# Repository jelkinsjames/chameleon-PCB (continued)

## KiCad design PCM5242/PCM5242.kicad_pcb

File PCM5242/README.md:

# PCM 5242

The [PCM5242](https://www.ti.com/product/PCM5242) is a 32-bit stereo DAC IC chip. Its datasheet can be found and downloaded [here](chameleon-PCB/PCM5242/pcm5242.pdf).

Here is a block diagram of the 5242 (taken from the datasheet):

The chip is capable of several sophisticated DSP processess organic to itself, but that is not what we are going to use it for in this project. 
More details about why and how we are using this chip are to follow. We will start with the basic outline of the chip to a level of understanding that you will need to operate it, and then move into details about how exactly it is used in this application. At the end of this document, you will be able to use the 5242 with the Chameleon to achieve your audio-processing goals.

# Inputs

# Outputs

# Clocking

# PCB Design Details

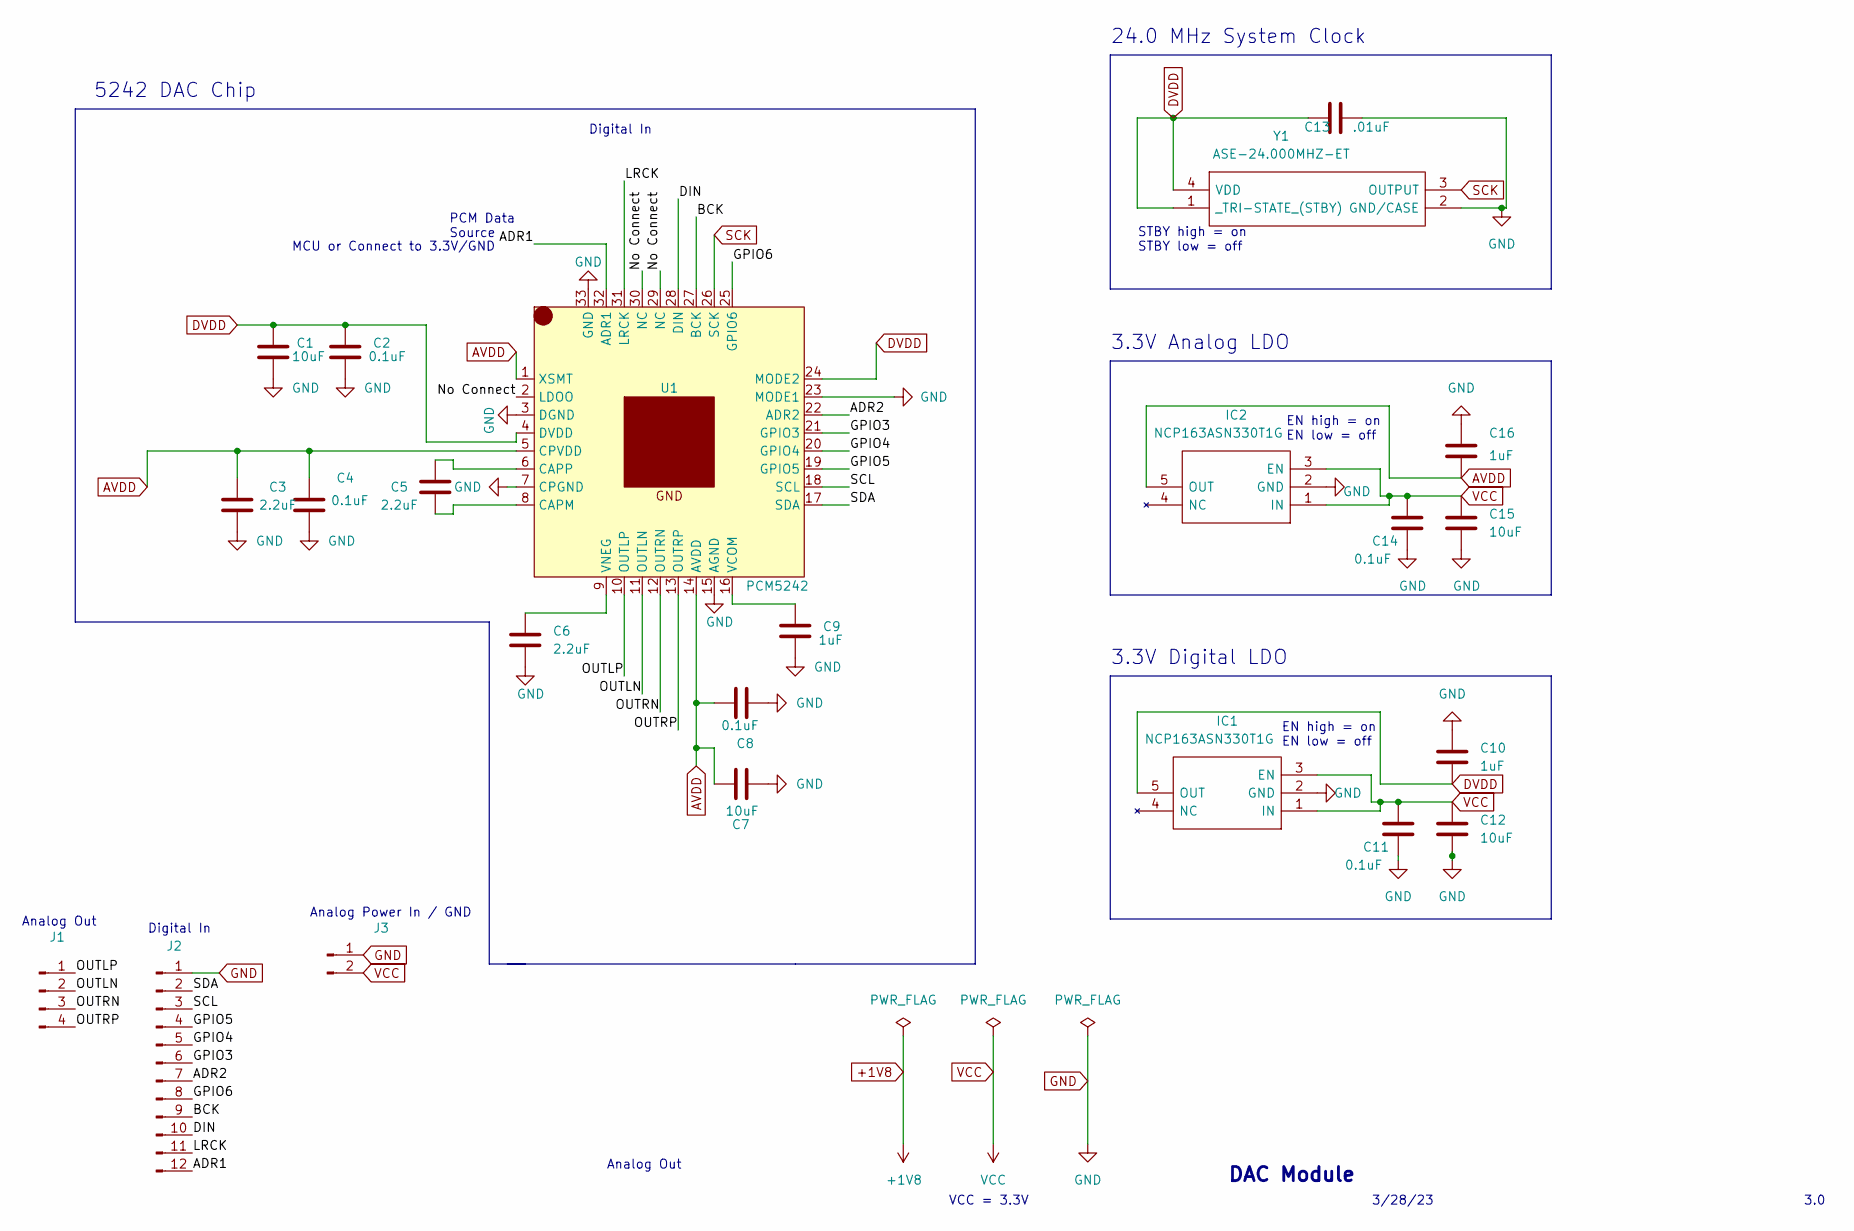
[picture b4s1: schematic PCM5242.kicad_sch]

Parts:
C1, C7, C12, C15: 10uF; C_0603_1608Metric_Pad1.08x0.95mm_HandSolder
C2, C4, C8, C11, C14: 0.1uF; C_0603_1608Metric_Pad1.08x0.95mm_HandSolder
C3, C5, C6: 2.2uF; C_0603_1608Metric_Pad1.08x0.95mm_HandSolder
C9, C10, C16: 1uF; C_0603_1608Metric_Pad1.08x0.95mm_HandSolder
C13: .01uF; C_0603_1608Metric_Pad1.08x0.95mm_HandSolder
IC1, IC2: NCP163ASN330T1G; SOT95P280X145-5N; Manufacturer_Part_Number NCP163ASN330T1G; Mouser Part Number 863-NCP163ASN330T1G
J1: Conn_01x04_Male; PinHeader_1x04_P2.54mm_Vertical
J2: Conn_01x12_Male; PinHeader_1x12_P2.54mm_Vertical
J3: d; PinHeader_1x02_P2.54mm_Vertical
U1: PCM5242; HVQFN-32-1EP_5x5mm_P0.5mm_EP3.1x3.1mm
Y1: ASE-24.000MHZ-ET; ASE24000MHZET; Manufacturer_Part_Number ASE-24.000MHZ-ET; Mouser Part Number 815-ASE24.000MHZET

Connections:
/ADR1: J2.12, U1.32 (ADR1)
/ADR2: J2.7, U1.22 (ADR2)
/BCK: J2.9, U1.27 (BCK)
/DIN: J2.10, U1.28 (DIN)
/GPIO3: J2.6, U1.21 (GPIO3)
/GPIO4: J2.5, U1.20 (GPIO4)
/GPIO5: J2.4, U1.19 (GPIO5)
/GPIO6: J2.8, U1.25 (GPIO6)
/LRCK: J2.11, U1.31 (LRCK)
/No Connect: U1.2 (LDOO), U1.29 (NC), U1.30 (NC)
/OUTLN: J1.2, U1.11 (OUTLN)
/OUTLP: J1.1, U1.10 (OUTLP)
/OUTRN: J1.3, U1.12 (OUTRN)
/OUTRP: J1.4, U1.13 (OUTRP)
/SCL: J2.3, U1.18 (SCL)
/SDA: J2.2, U1.17 (SDA)
AVDD: C3.1, C4.1, C7.1, C8.1, C16.2, IC2.5 (OUT), U1.1 (XSMT), U1.5 (CPVDD), U1.14 (AVDD)
DVDD: C1.2, C2.1, C10.2, C13.1, IC1.5 (OUT), U1.4 (DVDD), U1.24 (MODE2), Y1.1 (_TRI-STATE_(STBY)), Y1.4 (VDD)
GND: C1.1, C2.2, C3.2, C4.2, C6.2, C7.2, C8.2, C9.2, C10.1, C11.2, C12.2, C13.2, C14.2, C15.2, C16.1, IC1.2 (GND), IC2.2 (GND), J2.1, J3.1, U1.3 (DGND), U1.7 (CPGND), U1.15 (AGND), U1.23 (MODE1), U1.33 (GND), Y1.2 (GND/CASE)
unnamed: C5.1, U1.6 (CAPP)
unnamed: C5.2, U1.8 (CAPM)
unnamed: C6.1, U1.9 (VNEG)
unnamed: C9.1, U1.16 (VCOM)
SCK: U1.26 (SCK), Y1.3 (OUTPUT)
VCC: C11.1, C12.1, C14.1, C15.1, IC1.1 (IN), IC1.3 (EN), IC2.1 (IN), IC2.3 (EN), J3.2

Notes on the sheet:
Analog Out
Digital In
EN high = on EN low = off
3.0
Analog Power In / GND
3.3V Analog LDO
MCU or Connect to 3.3V/GND
24.0 MHz System Clock
STBY high = on STBY low = off
PCM Data Source
DAC Module
VCC = 3.3V
3.3V Digital LDO
Analog Out
Digital In
5242 DAC Chip
3/28/23

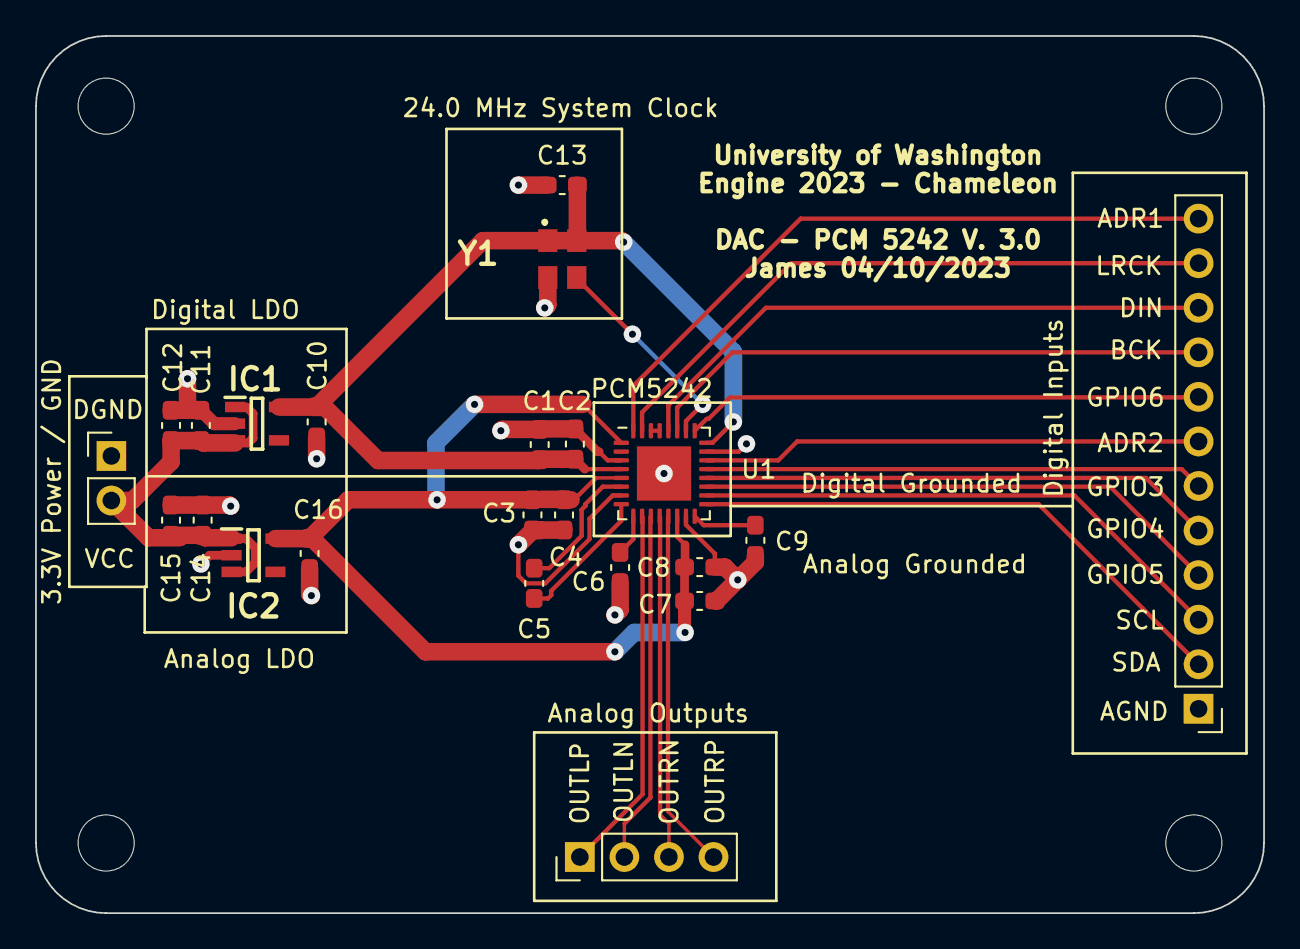
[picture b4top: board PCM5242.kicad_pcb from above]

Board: 2 copper layers, 70.0 x 50.0 mm, 23 parts (0 on the bottom side), 25 nets.

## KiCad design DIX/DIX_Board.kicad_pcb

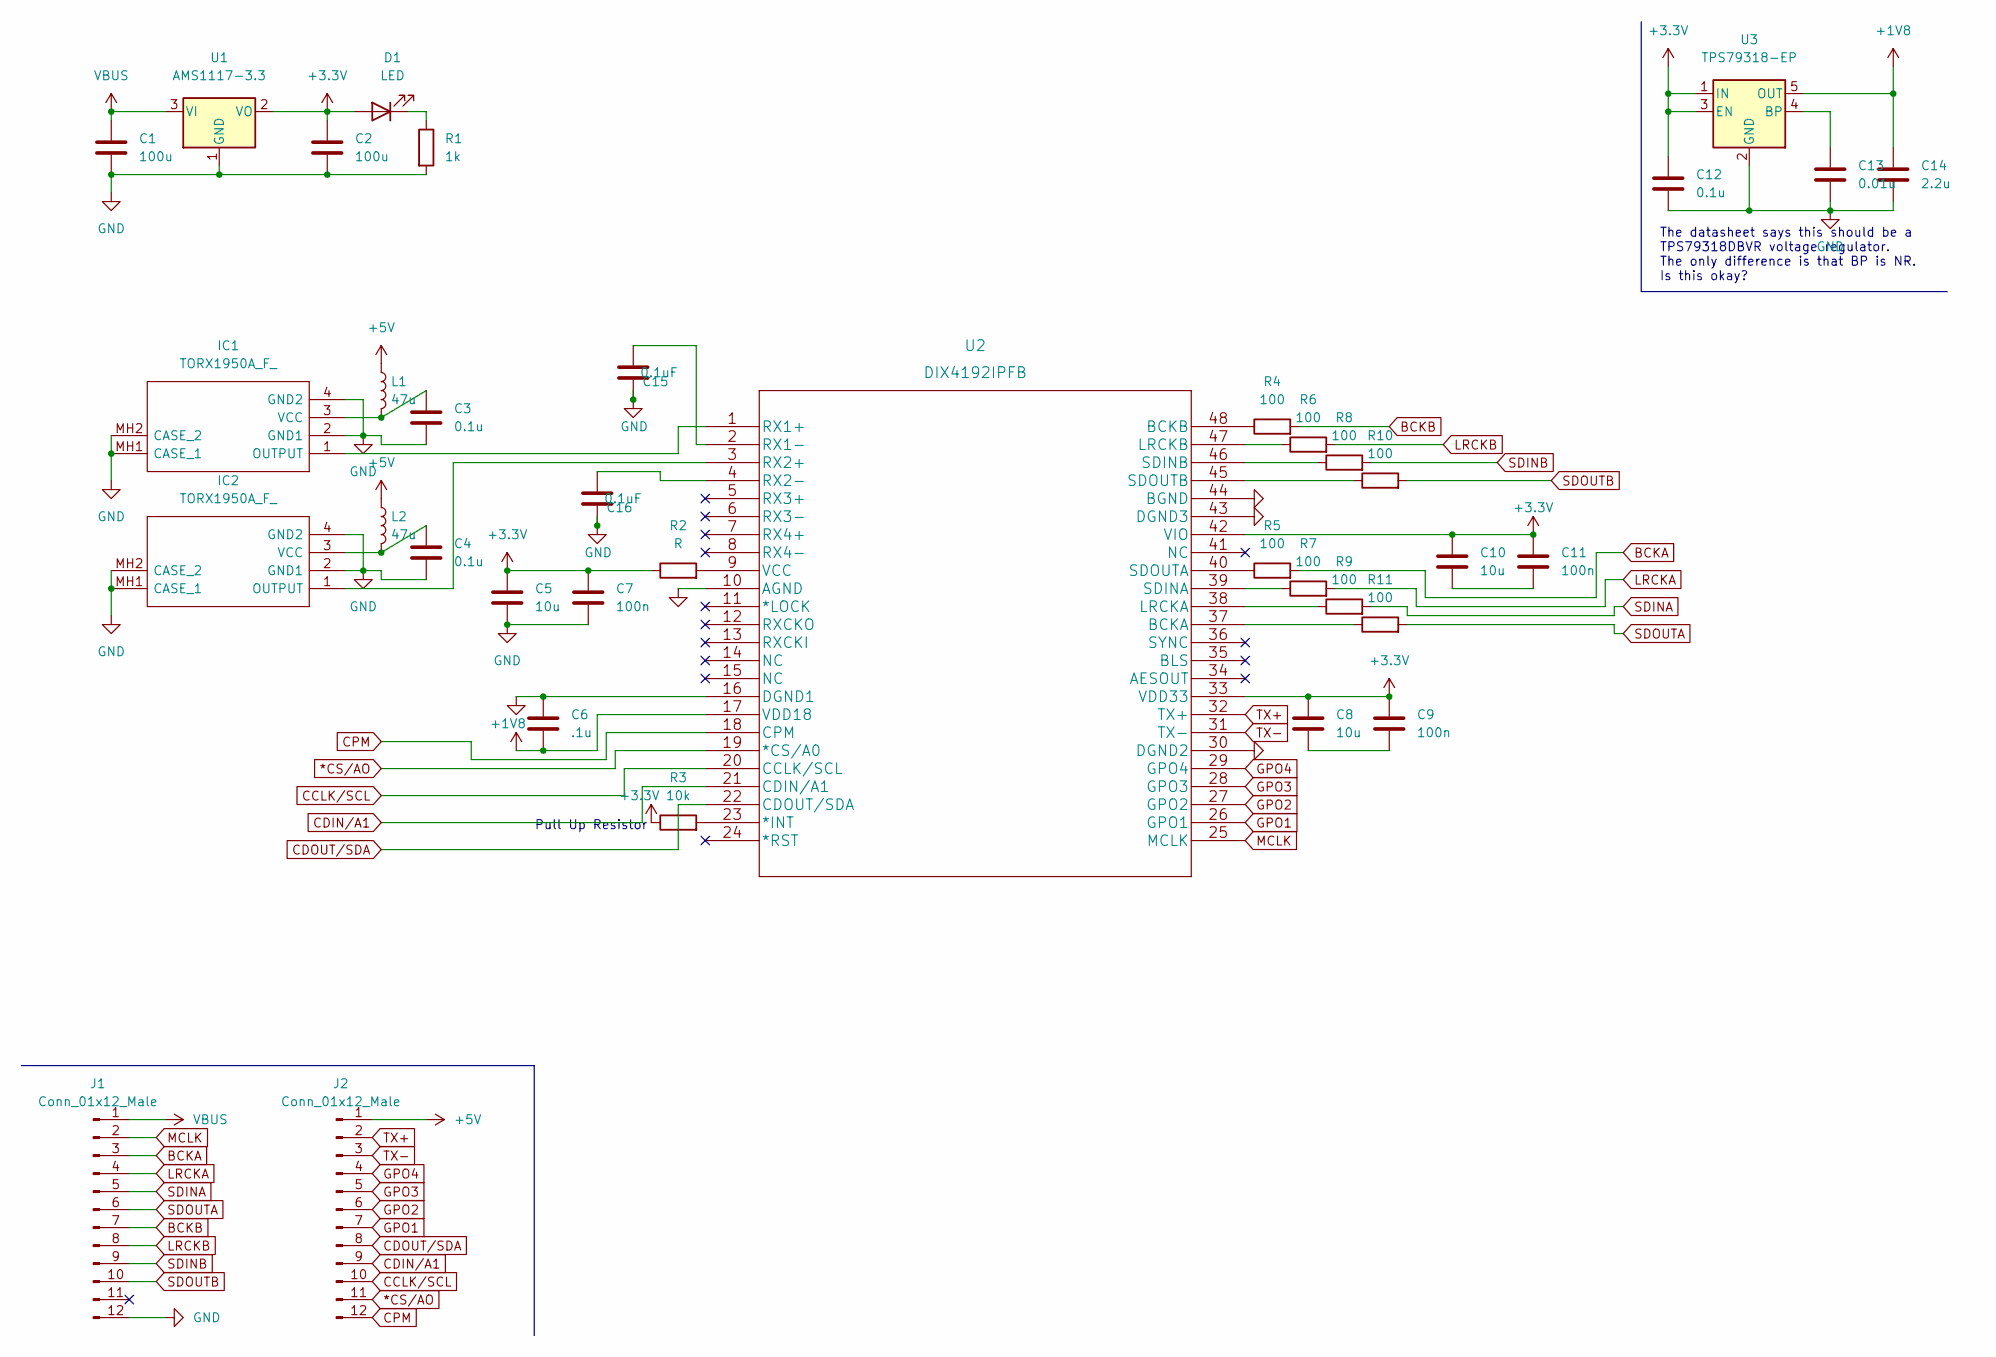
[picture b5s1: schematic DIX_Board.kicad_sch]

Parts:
C1, C2: 100u; C_0805_2012Metric_Pad1.18x1.45mm_HandSolder
C3, C4: 0.1u; C_0805_2012Metric_Pad1.18x1.45mm_HandSolder
C5, C8, C10: 10u; C_0805_2012Metric
C6: .1u; C_0805_2012Metric
C7, C9, C11: 100n; C_0805_2012Metric
C12: 0.1u; C_0805_2012Metric
C13: 0.01u; C_0805_2012Metric
C14: 2.2u; C_0805_2012Metric
C15, C16: 0.1uF; C_0603_1608Metric_Pad1.08x0.95mm_HandSolder
D1: LED; LED_D8.0mm
IC1, IC2: TORX1950A_F_; Reverb_BTDR-1H; Mouser Part Number 71-TORX1950A(F)
J1, J2: Conn_01x12_Male; PinHeader_1x12_P1.27mm_Vertical
L1, L2: 47u; L_0805_2012Metric_Pad1.05x1.20mm_HandSolder
R1: 1k; R_0805_2012Metric_Pad1.20x1.40mm_HandSolder
R2: R; R_0805_2012Metric_Pad1.20x1.40mm_HandSolder
R3: 10k; R_0805_2012Metric_Pad1.20x1.40mm_HandSolder
R4, R5, R6, R7, R8, R9, R10, R11: 100; R_0805_2012Metric_Pad1.20x1.40mm_HandSolder
U1: AMS1117-3.3; SOT-223-3_TabPin2
U2: DIX4192IPFB
U3: TPS79318-EP; SOT-23-5

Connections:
*CS/AO: J2.11, U2.19 (*CS/A0)
+1V8: C6.2, C14.1, U2.17 (VDD18), U3.5 (OUT)
+3.3V: C2.1, C5.1, C7.1, C8.1, C9.1, C10.1, C11.1, C12.1, D1.2 (A), R2.1, R3.1, U1.2 (VO), U2.33 (VDD33), U2.42 (VIO), U3.1 (IN), U3.3 (EN)
+5V: J2.1, L1.1, L2.1
BCKA: J1.3, R5.2
BCKB: J1.7, R4.2
CCLK/SCL: J2.10, U2.20 (CCLK/SCL)
CDIN/A1: J2.9, U2.21 (CDIN/A1)
CDOUT/SDA: J2.8, U2.22 (CDOUT/SDA)
CPM: J2.12, U2.18 (CPM)
GND: C1.2, C2.2, C3.2, C4.2, C5.2, C6.1, C7.2, C12.2, C13.2, C14.2, C15.1, C16.1, IC1.2 (GND1), IC1.4 (GND2), IC1.MH1 (CASE_1), IC1.MH2 (CASE_2), IC2.2 (GND1), IC2.4 (GND2), IC2.MH1 (CASE_1), IC2.MH2 (CASE_2), J1.12, R1.2, U1.1 (GND), U2.10 (AGND), U2.16 (DGND1), U2.30 (DGND2), U2.43 (DGND3), U2.44 (BGND), U3.2 (GND)
GPO1: J2.7, U2.26 (GPO1)
GPO2: J2.6, U2.27 (GPO2)
GPO3: J2.5, U2.28 (GPO3)
GPO4: J2.4, U2.29 (GPO4)
LRCKA: J1.4, R7.2
LRCKB: J1.8, R6.2
MCLK: J1.2, U2.25 (MCLK)
unnamed: C3.1, IC1.3 (VCC), L1.2
unnamed: C4.1, IC2.3 (VCC), L2.2
unnamed: C8.2, C9.2
unnamed: C10.2, C11.2
unnamed: C13.1, U3.4 (BP)
unnamed: C15.2, U2.2 (RX1-)
unnamed: C16.2, U2.4 (RX2-)
unnamed: D1.1 (K), R1.1
unnamed: IC1.1 (OUTPUT), U2.1 (RX1+)
unnamed: IC2.1 (OUTPUT), U2.3 (RX2+)
unnamed: R2.2, U2.9 (VCC)
unnamed: R3.2, U2.23 (*INT)
unnamed: R4.1, U2.48 (BCKB)
unnamed: R5.1, U2.40 (SDOUTA)
unnamed: R6.1, U2.47 (LRCKB)
unnamed: R7.1, U2.39 (SDINA)
unnamed: R8.1, U2.46 (SDINB)
unnamed: R9.1, U2.38 (LRCKA)
unnamed: R10.1, U2.45 (SDOUTB)
unnamed: R11.1, U2.37 (BCKA)
SDINA: J1.5, R9.2
SDINB: J1.9, R8.2
SDOUTA: J1.6, R11.2
SDOUTB: J1.10, R10.2
TX+: J2.2, U2.32 (TX+)
TX-: J2.3, U2.31 (TX-)
VBUS: C1.1, J1.1, U1.3 (VI)

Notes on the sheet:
The datasheet says this should be a TPS79318DBVR voltage regulator. The only difference is that BP is NR. Is this okay?
Pull Up Resistor

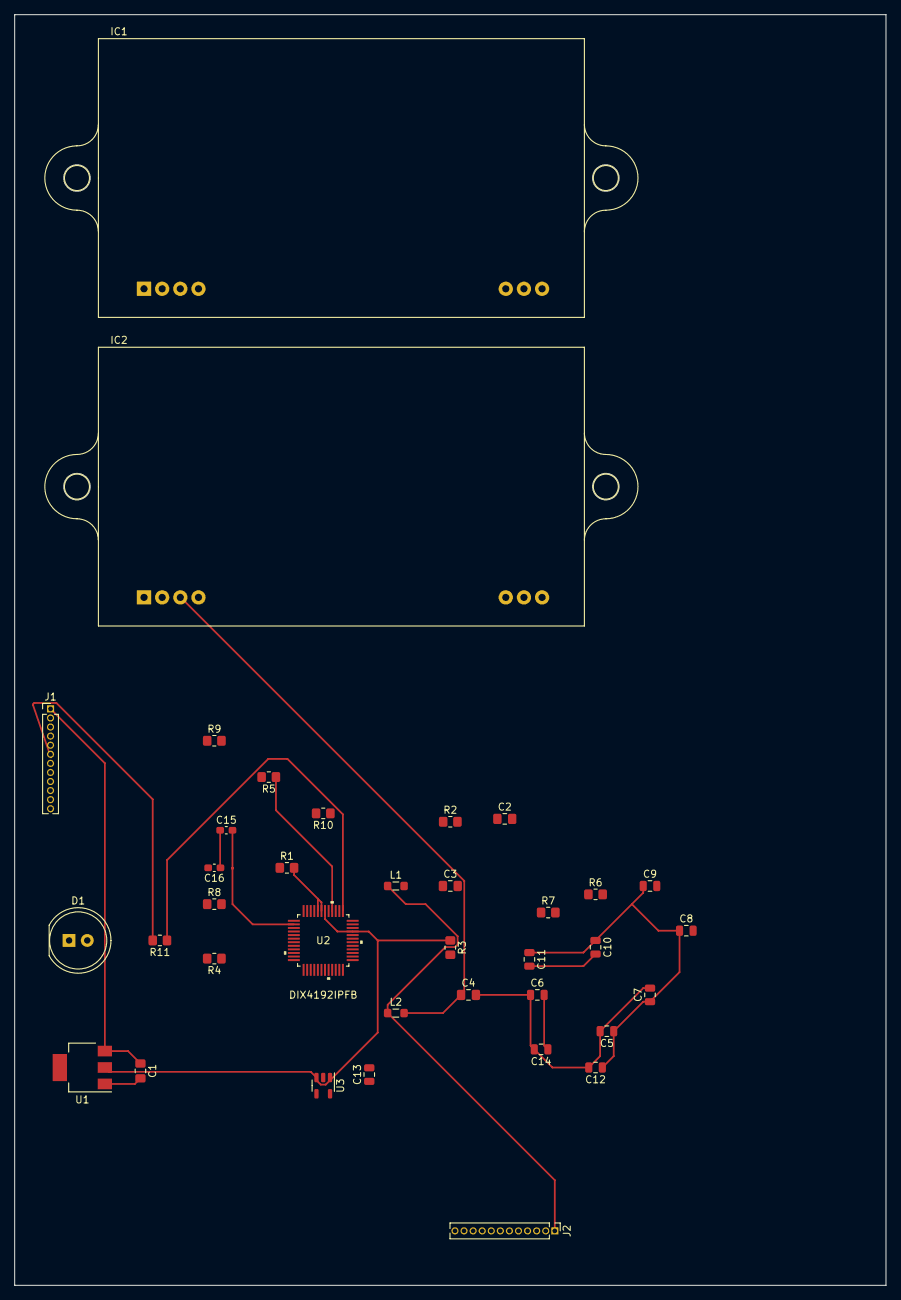
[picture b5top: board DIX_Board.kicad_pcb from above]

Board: 2 copper layers, 121.9 x 177.8 mm, 37 parts (0 on the bottom side), 45 nets.

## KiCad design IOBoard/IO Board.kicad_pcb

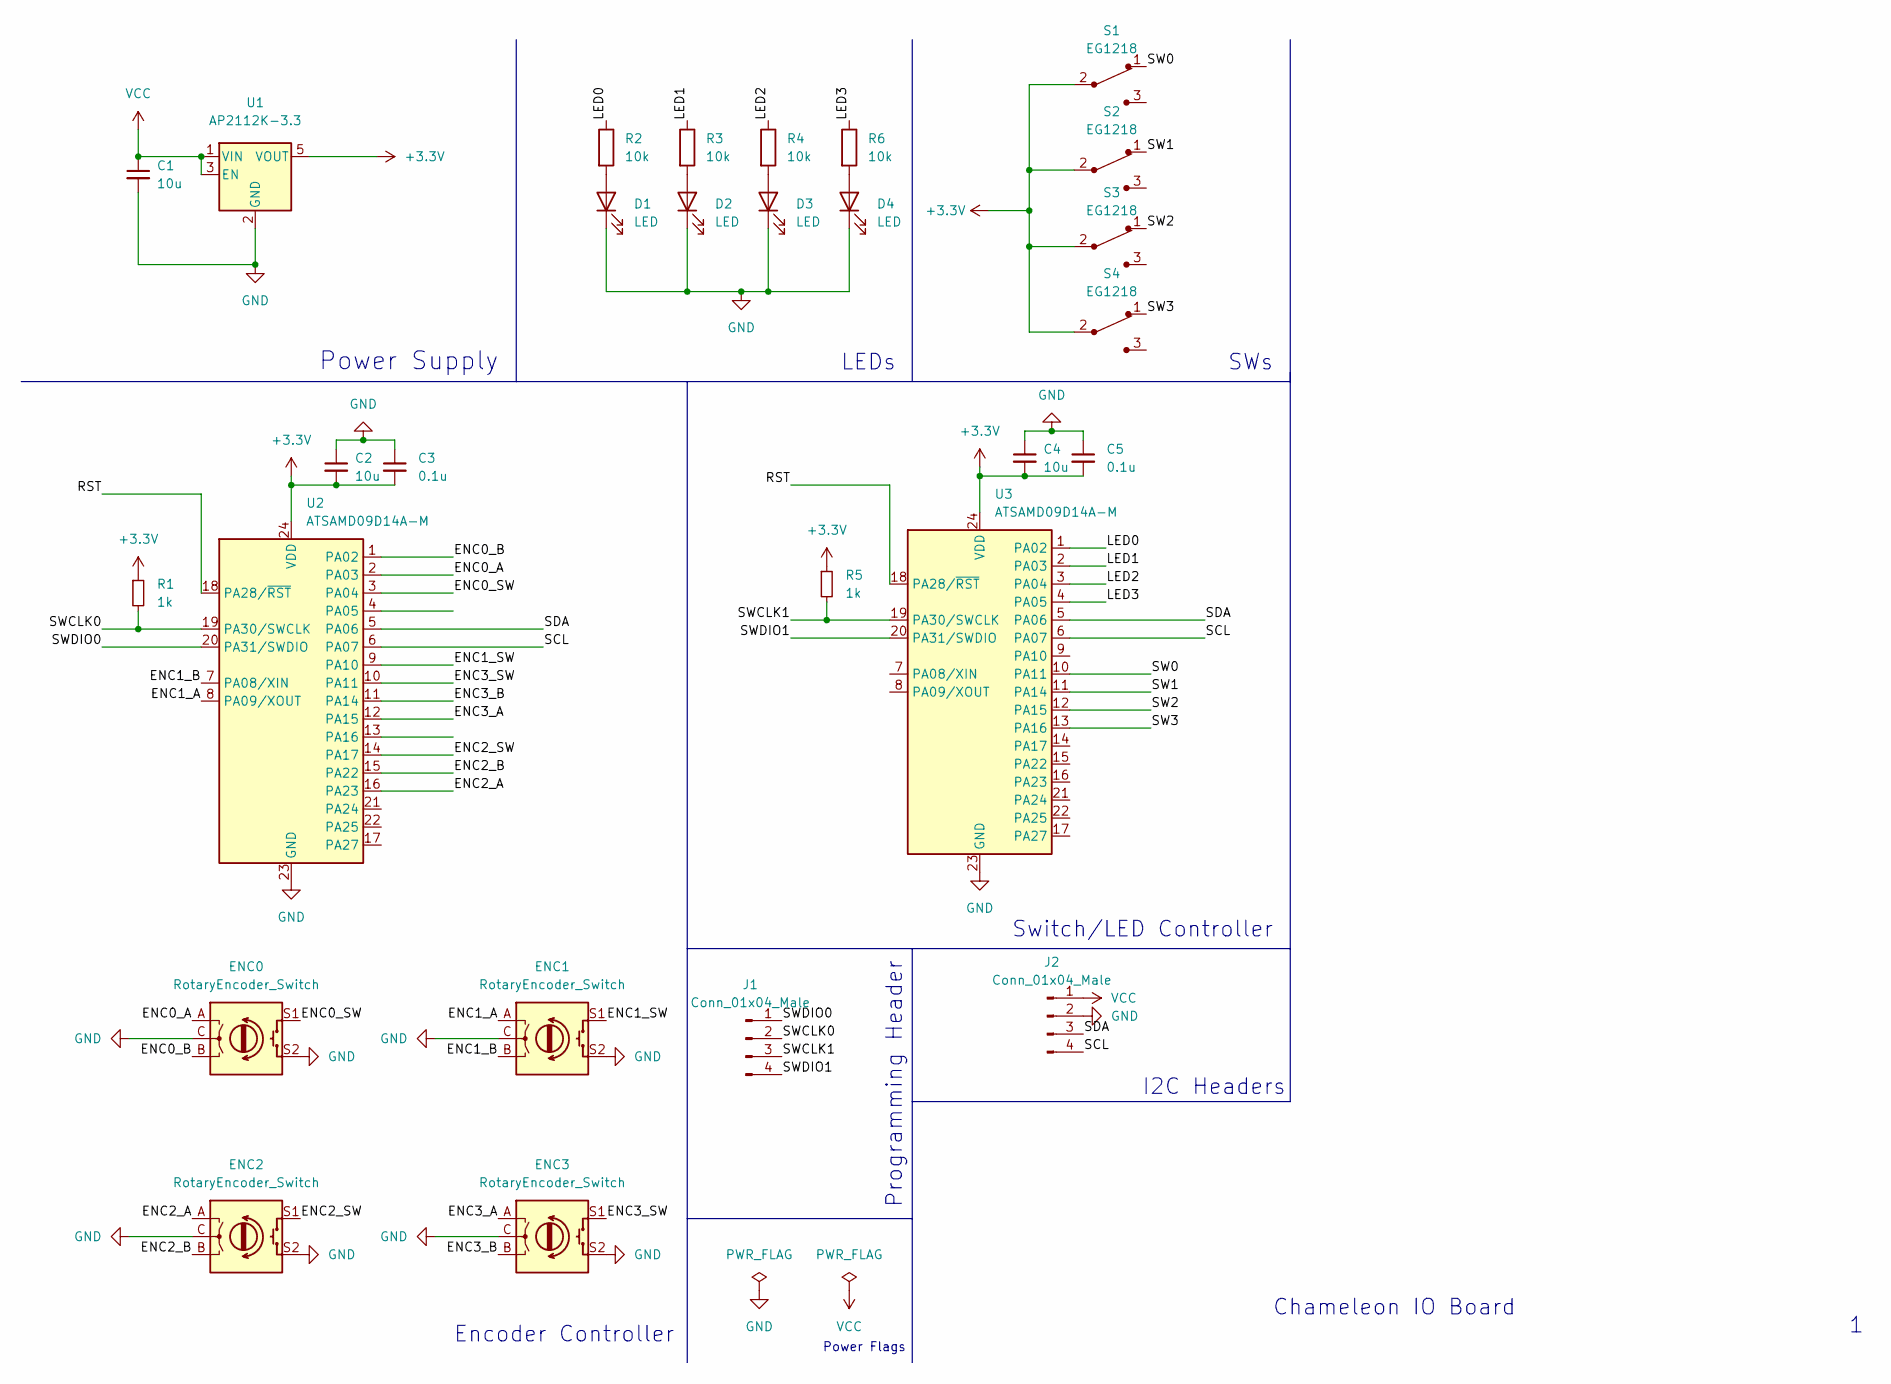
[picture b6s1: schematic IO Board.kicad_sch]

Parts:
C1, C2, C4: 10u; C_0201_0603Metric
C3, C5: 0.1u; C_0201_0603Metric
D1, D2, D3, D4: LED; LED_D3.0mm
ENC0, ENC1, ENC2, ENC3: RotaryEncoder_Switch; RotaryEncoder_Bourns_Vertical_PEC12R-3xxxF-Sxxxx
J1, J2: Conn_01x04_Male; PinHeader_1x04_P2.54mm_Vertical
R1, R5: 1k; R_0603_1608Metric
R2, R3, R4, R6: 10k; R_0603_1608Metric
S1, S2, S3, S4: EG1218; Switch_Slide_11.6x4mm_EG1218; MPN EG1218; Digi-Key_PN EG1903-ND
U1: AP2112K-3.3; SOT-23-5
U2, U3: ATSAMD09D14A-M; QFN-24-1EP_4x4mm_P0.5mm_EP2.6x2.6mm

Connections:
+3.3V: C2.2, C3.2, C4.2, C5.2, R1.1, R5.1, S1.2, S2.2, S3.2, S4.2, U1.5 (VOUT), U2.24 (VDD), U3.24 (VDD)
/ENC0_A: ENC0.A, U2.2 (PA03)
/ENC0_B: ENC0.B, U2.1 (PA02)
/ENC0_SW: ENC0.S1, U2.3 (PA04)
/ENC1_A: ENC1.A, U2.8 (PA09/XOUT)
/ENC1_B: ENC1.B, U2.7 (PA08/XIN)
/ENC1_SW: ENC1.S1, U2.9 (PA10)
/ENC2_A: ENC2.A, U2.16 (PA23)
/ENC2_B: ENC2.B, U2.15 (PA22)
/ENC2_SW: ENC2.S1, U2.14 (PA17)
/ENC3_A: ENC3.A, U2.12 (PA15)
/ENC3_B: ENC3.B, U2.11 (PA14)
/ENC3_SW: ENC3.S1, U2.10 (PA11)
/LED0: R2.1, U3.1 (PA02)
/LED1: R3.1, U3.2 (PA03)
/LED2: R4.1, U3.3 (PA04)
/LED3: R6.1, U3.4 (PA05)
/RST: U2.18 (PA28/~RST), U3.18 (PA28/~RST)
/SCL: J2.4, U2.6 (PA07), U3.6 (PA07)
/SDA: J2.3, U2.5 (PA06), U3.5 (PA06)
/SW0: S1.1, U3.10 (PA11)
/SW1: S2.1, U3.11 (PA14)
/SW2: S3.1, U3.12 (PA15)
/SW3: S4.1, U3.13 (PA16)
/SWCLK0: J1.2, R1.2, U2.19 (PA30/SWCLK)
/SWCLK1: J1.3, R5.2, U3.19 (PA30/SWCLK)
/SWDIO0: J1.1, U2.20 (PA31/SWDIO)
/SWDIO1: J1.4, U3.20 (PA31/SWDIO)
GND: C1.2, C2.1, C3.1, C4.1, C5.1, D1.1 (K), D2.1 (K), D3.1 (K), D4.1 (K), ENC0.C, ENC0.S2, ENC1.C, ENC1.S2, ENC2.C, ENC2.S2, ENC3.C, ENC3.S2, J2.2, U1.2 (GND), U2.23 (GND), U3.23 (GND)
unnamed: D1.2 (A), R2.2
unnamed: D2.2 (A), R3.2
unnamed: D3.2 (A), R4.2
unnamed: D4.2 (A), R6.2
VCC: C1.1, J2.1, U1.1 (VIN), U1.3 (EN)

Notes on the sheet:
SWs
Switch/LED Controller
I2C Headers
Power Flags
Chameleon IO Board
Encoder Controller
LEDs
Power Supply
Programming Header

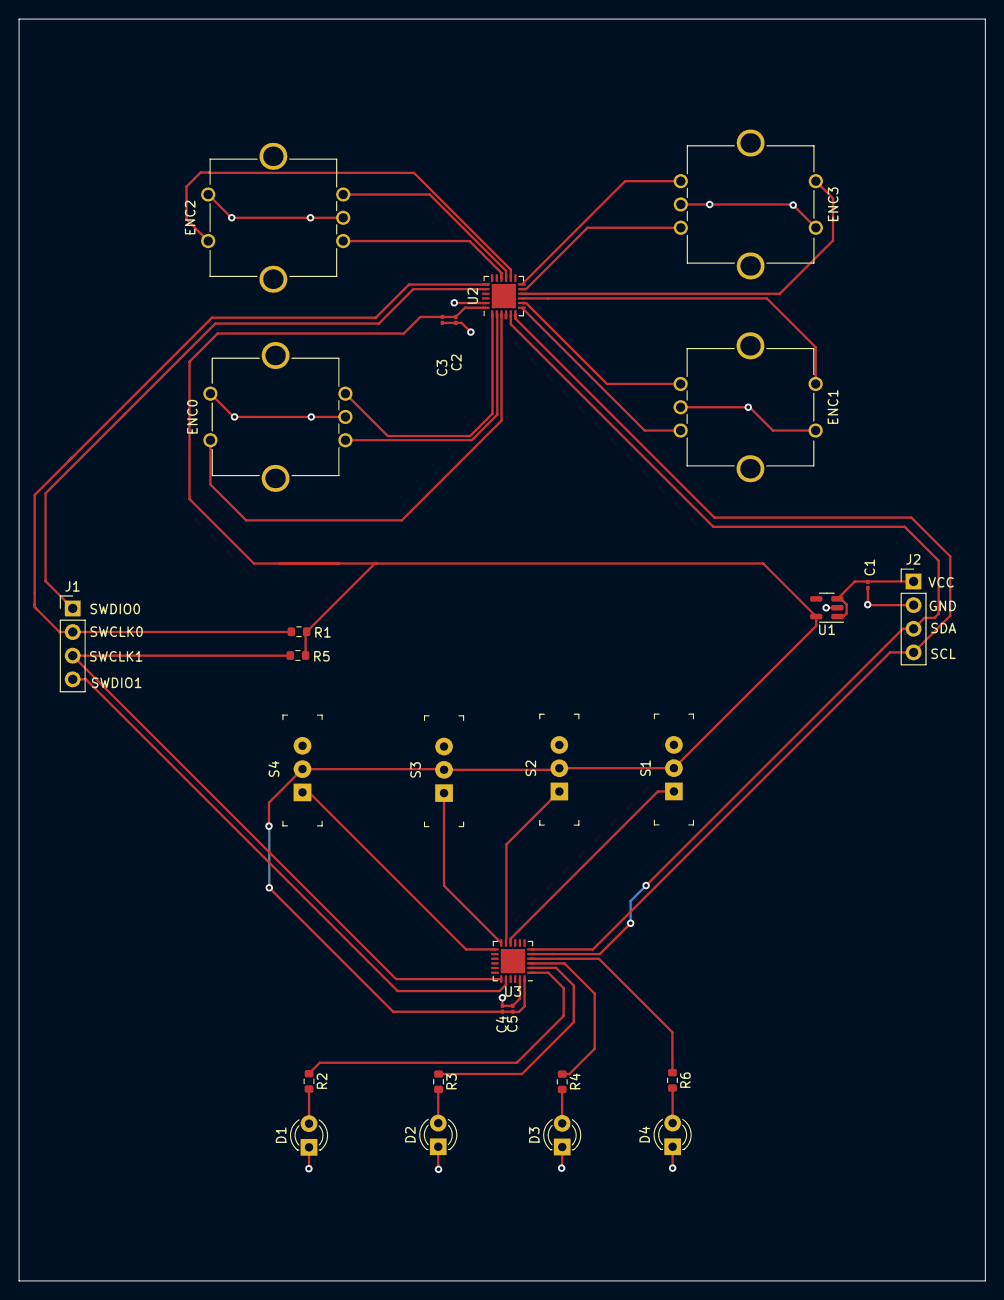
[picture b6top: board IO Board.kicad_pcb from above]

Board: 2 copper layers, 103.8 x 135.5 mm, 28 parts (0 on the bottom side), 34 nets.

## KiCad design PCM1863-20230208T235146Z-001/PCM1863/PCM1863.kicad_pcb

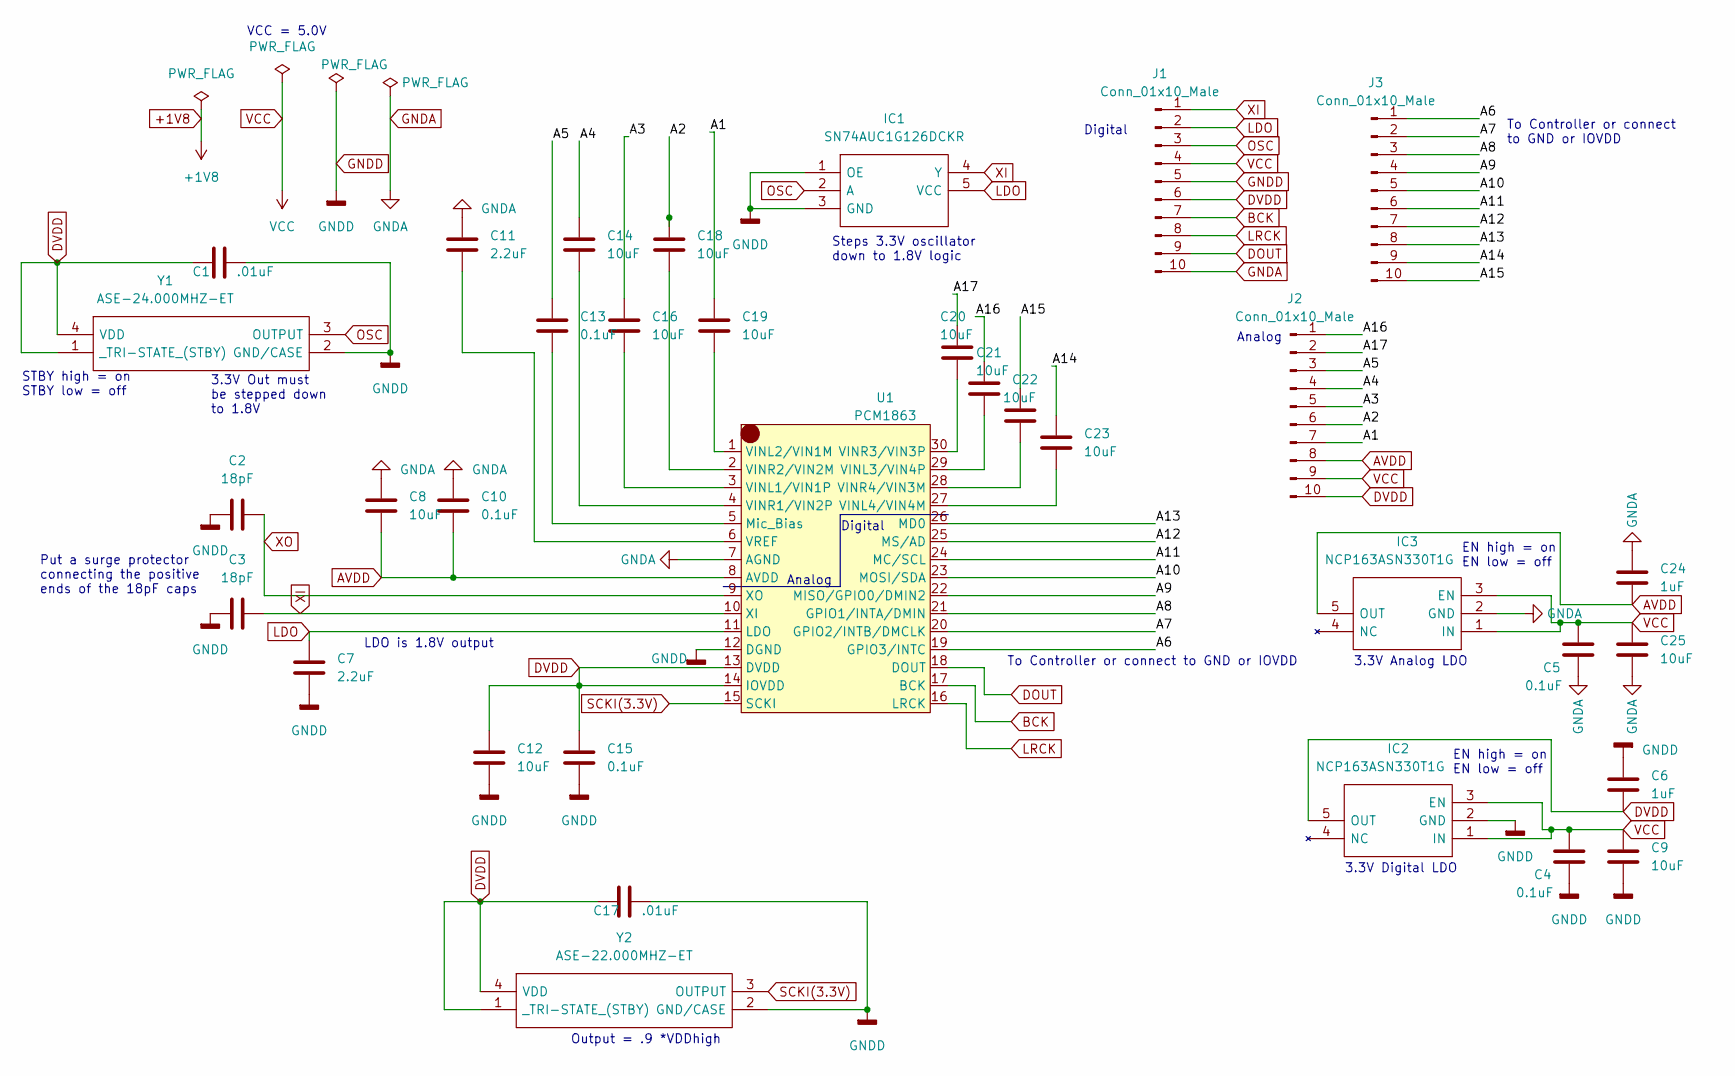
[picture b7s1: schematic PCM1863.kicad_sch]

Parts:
C1, C17: .01uF; C_0603_1608Metric_Pad1.08x0.95mm_HandSolder
C2, C3: 18pF; C_0603_1608Metric_Pad1.08x0.95mm_HandSolder
C4, C5, C10, C13, C15: 0.1uF; C_0603_1608Metric_Pad1.08x0.95mm_HandSolder
C6, C24: 1uF; C_0603_1608Metric_Pad1.08x0.95mm_HandSolder
C7, C11: 2.2uF; C_0603_1608Metric_Pad1.08x0.95mm_HandSolder
C8, C9, C12, C14, C16, C18, C19, C20, C21, C22, C23, C25: 10uF; C_0603_1608Metric_Pad1.08x0.95mm_HandSolder
IC1: SN74AUC1G126DCKR; SOT65P210X110-5N; Manufacturer_Part_Number SN74AUC1G126DCKR; Mouser Part Number 595-SN74AUC1G126DCKR
IC2, IC3: NCP163ASN330T1G; SOT95P280X145-5N; Manufacturer_Part_Number NCP163ASN330T1G; Mouser Part Number 863-NCP163ASN330T1G
J1, J2, J3: Conn_01x10_Male; PinHeader_1x10_P2.54mm_Vertical
U1: PCM1863; PCM1863QDBTRQ1
Y1: ASE-24.000MHZ-ET; ASE24000MHZET; Manufacturer_Part_Number ASE-24.000MHZ-ET; Mouser Part Number 815-ASE24.000MHZET
Y2: ASE-22.000MHZ-ET; ASE24000MHZET; Manufacturer_Part_Number ASE-24.000MHZ-ET; Mouser Part Number 815-ASE24.000MHZET

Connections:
/A1: C19.1, J2.7
/A2: C18.1, J2.6
/A3: C16.1, J2.5
/A4: C14.1, J2.4
/A5: C13.1, J2.3
/A6: J3.1, U1.19 (GPIO3/INTC)
/A7: J3.2, U1.20 (GPIO2/INTB/DMCLK)
/A8: J3.3, U1.21 (GPIO1/INTA/DMIN)
/A9: J3.4, U1.22 (MISO/GPIO0/DMIN2)
/A10: J3.5, U1.23 (MOSI/SDA)
/A11: J3.6, U1.24 (MC/SCL)
/A12: J3.7, U1.25 (MS/AD)
/A13: J3.8, U1.26 (MD0)
/A14: C23.1, J3.9
/A15: C22.1, J3.10
/A16: C21.1, J2.1
/A17: C20.1, J2.2
AVDD: C8.2, C10.2, C24.2, IC3.5 (OUT), J2.8, U1.8 (AVDD)
BCK: J1.7, U1.17 (BCK)
DOUT: J1.9, U1.18 (DOUT)
DVDD: C1.1, C6.2, C12.1, C15.1, C17.1, IC2.5 (OUT), J1.6, J2.10, U1.13 (DVDD), U1.14 (IOVDD), Y1.1 (_TRI-STATE_(STBY)), Y1.4 (VDD), Y2.1 (_TRI-STATE_(STBY)), Y2.4 (VDD)
GNDA: C5.2, C8.1, C10.1, C11.1, C24.1, C25.2, IC3.2 (GND), J1.10, U1.7 (AGND)
GNDD: C1.2, C2.1, C3.1, C4.2, C6.1, C7.2, C9.2, C12.2, C15.2, C17.2, IC1.1 (OE), IC1.3 (GND), IC2.2 (GND), J1.5, U1.12 (DGND), Y1.2 (GND/CASE), Y2.2 (GND/CASE)
LDO: C7.1, IC1.5 (VCC), J1.2, U1.11 (LDO)
LRCK: J1.8, U1.16 (LRCK)
unnamed: C11.2, U1.6 (VREF)
unnamed: C13.2, U1.5 (Mic_Bias)
unnamed: C14.2, U1.4 (VINR1/VIN2P)
unnamed: C16.2, U1.3 (VINL1/VIN1P)
unnamed: C18.2, U1.2 (VINR2/VIN2M)
unnamed: C19.2, U1.1 (VINL2/VIN1M)
unnamed: C20.2, U1.30 (VINR3/VIN3P)
unnamed: C21.2, U1.29 (VINL3/VIN4P)
unnamed: C22.2, U1.28 (VINR4/VIN3M)
unnamed: C23.2, U1.27 (VINL4/VIN4M)
OSC: IC1.2 (A), J1.3, Y1.3 (OUTPUT)
SCKI(3.3V): U1.15 (SCKI), Y2.3 (OUTPUT)
VCC: C4.1, C5.1, C9.1, C25.1, IC2.1 (IN), IC2.3 (EN), IC3.1 (IN), IC3.3 (EN), J1.4, J2.9
XI: C3.2, IC1.4 (Y), J1.1, U1.10 (XI)
XO: C2.2, U1.9 (XO)

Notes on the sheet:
Digital
Analog
STBY high = on STBY low = off
LDO is 1.8V output
3.3V Analog LDO
3.3V Out must be stepped down to 1.8V
EN high = on EN low = off
3.3V Digital LDO
VCC = 5.0V
Steps 3.3V oscillator down to 1.8V logic
To Controller or connect to GND or IOVDD
Put a surge protector connecting the positive ends of the 18pF caps
To Controller or connect to GND or IOVDD
Output = .9 *VDDhigh

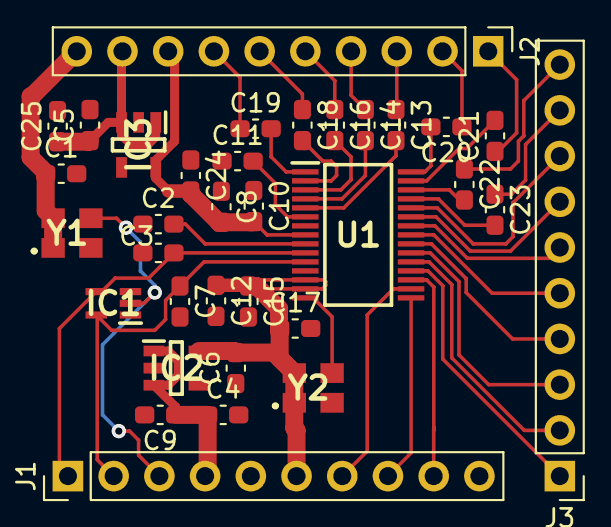
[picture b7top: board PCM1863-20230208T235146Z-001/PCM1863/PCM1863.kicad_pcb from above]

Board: 2 copper layers, 34 parts (0 on the bottom side), 40 nets.

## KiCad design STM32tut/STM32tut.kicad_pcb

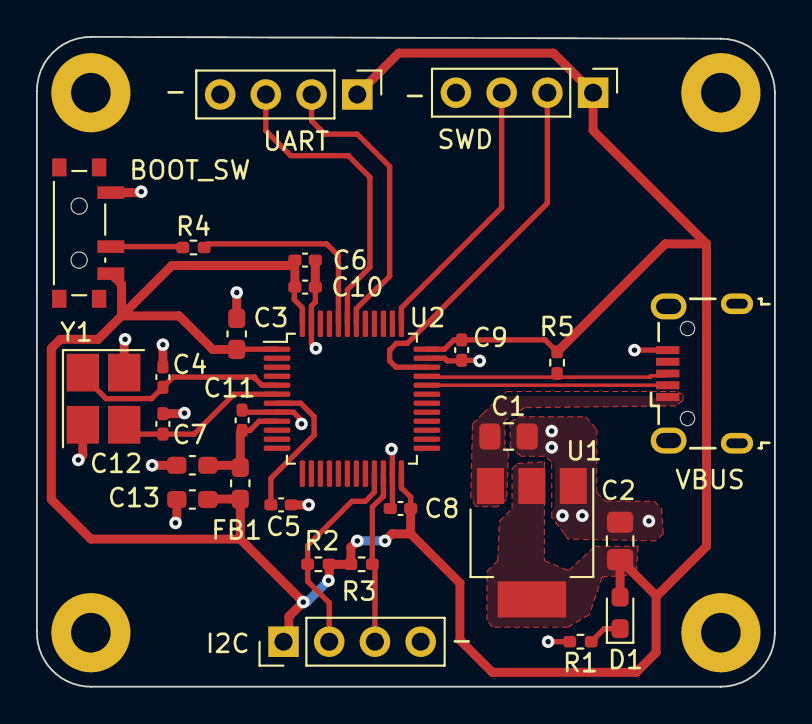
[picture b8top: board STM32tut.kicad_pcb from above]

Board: 2 copper layers, 41.0 x 36.1 mm, 32 parts (0 on the bottom side), 18 nets.

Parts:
C1, C2: 22uF; C_0805_2012Metric_Pad1.18x1.45mm_HandSolder
C3: 10uF; C_0603_1608Metric_Pad1.08x0.95mm_HandSolder
C4, C7: 10pF; C_0402_1005Metric_Pad0.74x0.62mm_HandSolder
C5, C6, C8, C9, C10: 100nF; C_0402_1005Metric_Pad0.74x0.62mm_HandSolder
C11: 10nF; C_0402_1005Metric_Pad0.74x0.62mm_HandSolder
C12, C13: 1uF; C_0603_1608Metric_Pad1.08x0.95mm_HandSolder
D1: RED1.8; LED_0603_1608Metric_Pad1.05x0.95mm_HandSolder
FB1: 120R; L_0603_1608Metric_Pad1.05x0.95mm_HandSolder
H1, H2, H3, H4: MountingHole_Pad; MountingHole_2.2mm_M2_Pad
J1, J2, J3: Conn_01x04_Male; PinHeader_1x04_P2.54mm_Vertical
J4: USB_B_Micro; USB_Micro-B_Wuerth_629105150521
R1, R2, R3, R5: 1.5k; R_0402_1005Metric_Pad0.72x0.64mm_HandSolder
R4: 10k; R_0402_1005Metric_Pad0.72x0.64mm_HandSolder
SW1: SW_SPDT; SW_SPDT_PCM12
U1: AMS1117-3.3; SOT-223-3_TabPin2
U2: STM32F103C8T6; LQFP-48_7x7mm_P0.5mm
Y1: 16MHz; Crystal_SMD_3225-4Pin_3.2x2.5mm_HandSoldering

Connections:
+3.3VA: C11.1, C12.1, FB1.1, U2.9 (VDDA)
+3V3: C2.1, C3.1, C6.1, C8.1, C9.1, C10.1, C13.1, D1.2 (A), FB1.2, J1.1, J2.1, J3.1, R2.1, R3.1, R5.1, SW1.3 (C), U1.2 (VO), U2.1 (VBAT), U2.24 (VDD), U2.36 (VDD), U2.48 (VDD)
/BOOT0: R4.2, U2.44 (BOOT0)
/HSE_IN: C4.1, U2.5 (PD0), Y1.1
/HSE_OUT: C7.1, U2.6 (PD1), Y1.3
/I2C2_SCL: J2.2, R2.2, U2.21 (PB10)
/I2C2_SDA: J2.3, R3.2, U2.22 (PB11)
/NRST: C5.1, U2.7 (NRST)
/POWER_LED_K: D1.1 (K), R1.1
/SWCLK: J3.3, U2.37 (PA14)
/SWDIO: J3.2, U2.34 (PA13)
/SW_BOOT0: R4.1, SW1.2 (B)
/UART1_RX: J1.3, U2.43 (PB7)
/UART1_TX: J1.2, U2.42 (PB6)
/USB_D+: J4.3 (D+), R5.2, U2.33 (PA12)
/USB_D-: J4.2 (D-), U2.32 (PA11)
GND: C1.2, C2.2, C3.2, C4.2, C5.2, C6.2, C7.2, C8.2, C9.2, C10.2, C11.2, C12.2, C13.2, H1.1, H2.1, H3.1, H4.1, J1.4, J2.4, J3.4, J4.5 (GND), R1.2, SW1.1 (A), U1.1 (GND), U2.8 (VSSA), U2.23 (VSS), U2.35 (VSS), U2.47 (VSS), Y1.2, Y1.4
VBUS: C1.1, J4.1 (VBUS), U1.3 (VI)

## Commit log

2023-02-12 Add files via upload
    Some progress was made on the PCB and schematic should be finished. Everything is placed, now I need to route and make the ground pours.
2023-02-12 adding 1863 V2
2023-02-14 Update PCB
    Almost finished routing and pouring, I have several questions for the meeting tomorrow luckily!
2023-02-14 Updated PCB
    Almost finished routing and pouring, I have some design questions for tomorrow.
2023-02-14 Delete PCM5242 directory
    Accidentally made this.
2023-02-15 tutorial part added
2023-02-15 finished tut
2023-02-15 1863 power added and schematic updated
2023-02-15 PCB placement no trace
2023-02-16 adc v3 complete
2023-02-16 fix typo in adc
2023-02-16 fix analog too close to digital
2023-02-17 added jumpers
2023-02-17 IOBoard Added
2023-02-17 schematic updates for ADC
2023-02-17 pcb grouping
2023-02-20 finished ADC v.4
2023-02-21 IO Board PCB updated
2023-02-21 adc update
2023-02-22 updating readme
2023-02-22 added PCM1863 readme
2023-02-25 misc updates
2023-02-25 DIX Board Start (Max Version)
    Just a start here....
2023-02-27 IOBoard PCB v1
2023-02-28 Max Version of DIX board
2023-02-28 IOBoard ATSAMD21 V1 added
2023-02-28 More! Stuff!
    Started on the actual board. Lots to learn.
2023-02-28 Less electrical check failures
2023-03-01 readme work
2023-03-01 IO Board Silkscreening Finished
2023-03-01 readme updates
2023-03-06 Some routing
2023-03-06 readme clocking update
2023-03-07 Rename
    Changed to fit general format
2023-03-07 Uploaded new 5242
    Realized my 5242 was out of date, uploaded new folder
2023-03-07 Delete Old 5242 Folder
    No longer needed
2023-03-07 Upload datasheet
    Uploaded datasheet
2023-03-07 Update README.md
    Added my 5242 readme
2023-03-07 Update README.md
    Updated to fix readme
2023-03-09 updating lab PC
2023-03-09 good readme
2023-03-12 schematic v5
2023-03-12 v5 finished
2023-03-17 adc v5
2023-03-27 adc setup guide
2023-03-27 deletes
2023-03-27 test images
2023-03-27 image stuff
2023-03-27 y no work
2023-03-27 try again
2023-03-27 give up on images
2023-03-28 .zip
2023-03-28 splitting up README
2023-03-28 readmes split
2023-03-28 progress
2023-03-30 Transmitter board V 1.01
2023-03-30 DAC 3.0 V1
2023-03-31 IOBoard V2 + documentation
2023-03-31 IO Board v2 + documentation
2023-04-03 updated potato os
2023-04-03 typo
2023-04-05 generated V2 Gerber/Drill Files
2023-04-07 io board updates
2023-04-07 Upload MPLAB Project
    Uploaded MPLAP project for Todd - Julian
2023-04-07 updated 5242, removed old folder
    I have revamped my PCB design, about 90% to new design (just missing silkscreens)
2023-04-07 temp
2023-04-08 Revert "Merge remote-tracking branch 'upstream/main'"
    This reverts commit 91e618c32c18b3f8ce9c65181e2c7ed2aa69dacd, reversing
    changes made to 5f9fe177db78953ec4a0d750e6893e90b3881885.
2023-04-08 Revert "Revert "Merge remote-tracking branch 'upstream/main'""
    This reverts commit 1d57ca07421005fad3c6f783a10b39dbb3c17bbf.
2023-04-10 5242 PCB v.3 Update
    Finished V.3. Should have correct footprints, pinouts for analog, good labeling.
2023-04-10 registers
2023-04-15 adc v6
2023-04-16 Transmitter is uploaded
2023-04-16 fixed files
2023-04-16 Version 3 transmitter
2023-04-16 fixed power plane
2023-04-17 Version 3.2 of Transmitter. Ready to order
2023-04-17 roubd edges
2023-04-22 plz work
2023-04-23 init commands
2023-04-23 directions for julian
2023-04-25 restore DAC
2023-04-27 added dimensions to f.fab layer
2023-04-27 added dimensions to PCB
2023-05-10 mch streamer files
2023-05-12 testing
2023-05-18 cleaned up'
2023-05-18 jack
2023-05-18 added firmware
2023-05-19 single_ended I/O
2023-05-19 fix SE add
2023-05-19 giving up on differential for now
2023-05-19 adc update to match IO
2023-05-19 adding libraries
2023-05-19 IOBoard v3 WIP
2023-05-19 manual libraries
2023-05-19 custom libraries
2023-05-21 IO Board v3
2023-05-22 changing io
2023-05-22 adc images
2023-05-22 DAC restored
2023-05-22 added IO Board dimensions
2023-05-27 updated README: added instructions for addressing LEDs
2023-05-27 Updated README: Fixed Links
2023-05-27 Fixed README Links
2023-06-08 fixed bitwise operations
